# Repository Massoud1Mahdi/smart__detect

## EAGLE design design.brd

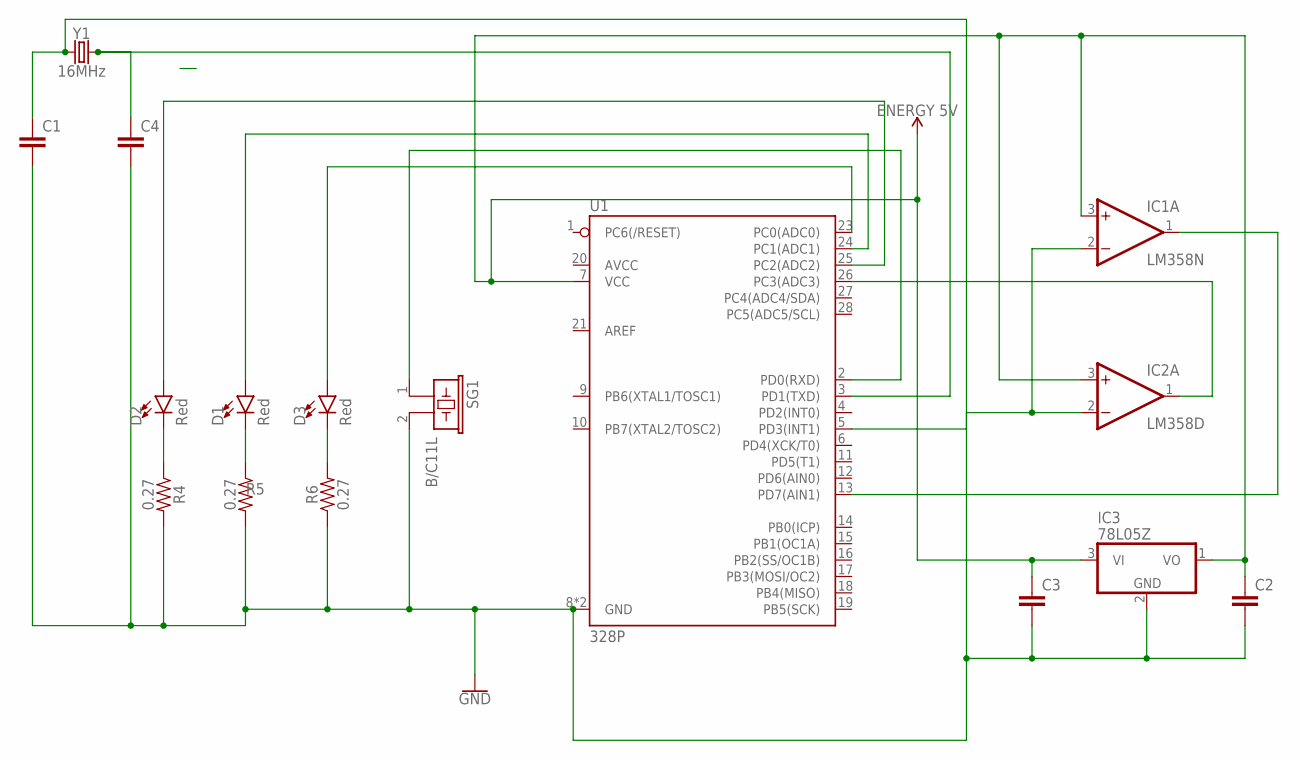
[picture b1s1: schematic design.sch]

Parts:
C1, C2, C3, C4: C2,5-3; C2.5-3
D1, D2, D3: Red; LED-0603
IC1: LM358N; DIL08
IC2: LM358D; SO08
IC3: 78L05Z; TO92
R4, R5, R6: 0.27; 0603
SG1: B/C11L
U1: 328P; DIP28
Y1: 16MHz; HC49US

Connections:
GND: C1.2, C2.2, C3.2, C4.2, IC1.2 (-IN), IC2.2 (-IN), IC3.2 (GND), R4.2, R5.2, R6.1, SG1.2, U1.8 (GND), U1.22 (GND)
unnamed: IC2.1 (OUT), U1.26 (PC3(ADC3))
unnamed: D2.C, R4.1
unnamed: D1.C, R5.1
unnamed: D3.C, R6.2
unnamed: D2.A, U1.25 (PC2(ADC2))
unnamed: D3.A, U1.23 (PC0(ADC0))
unnamed: D1.A, U1.24 (PC1(ADC1))
unnamed: SG1.1, U1.2 (PD0(RXD))
unnamed: C4.1, U1.3 (PD1(TXD)), Y1.2
unnamed: C1.1, U1.5 (PD3(INT1)), Y1.1
unnamed: IC1.1 (OUT), U1.13 (PD7(AIN1))
V+: IC1.8 (V+), IC2.8 (V+)
V-: IC1.4 (V-), IC2.4 (V-)
V_BATT: C2.1, C3.1, IC1.3 (+IN), IC2.3 (+IN), IC3.1 (VO), IC3.3 (VI), U1.7 (VCC)

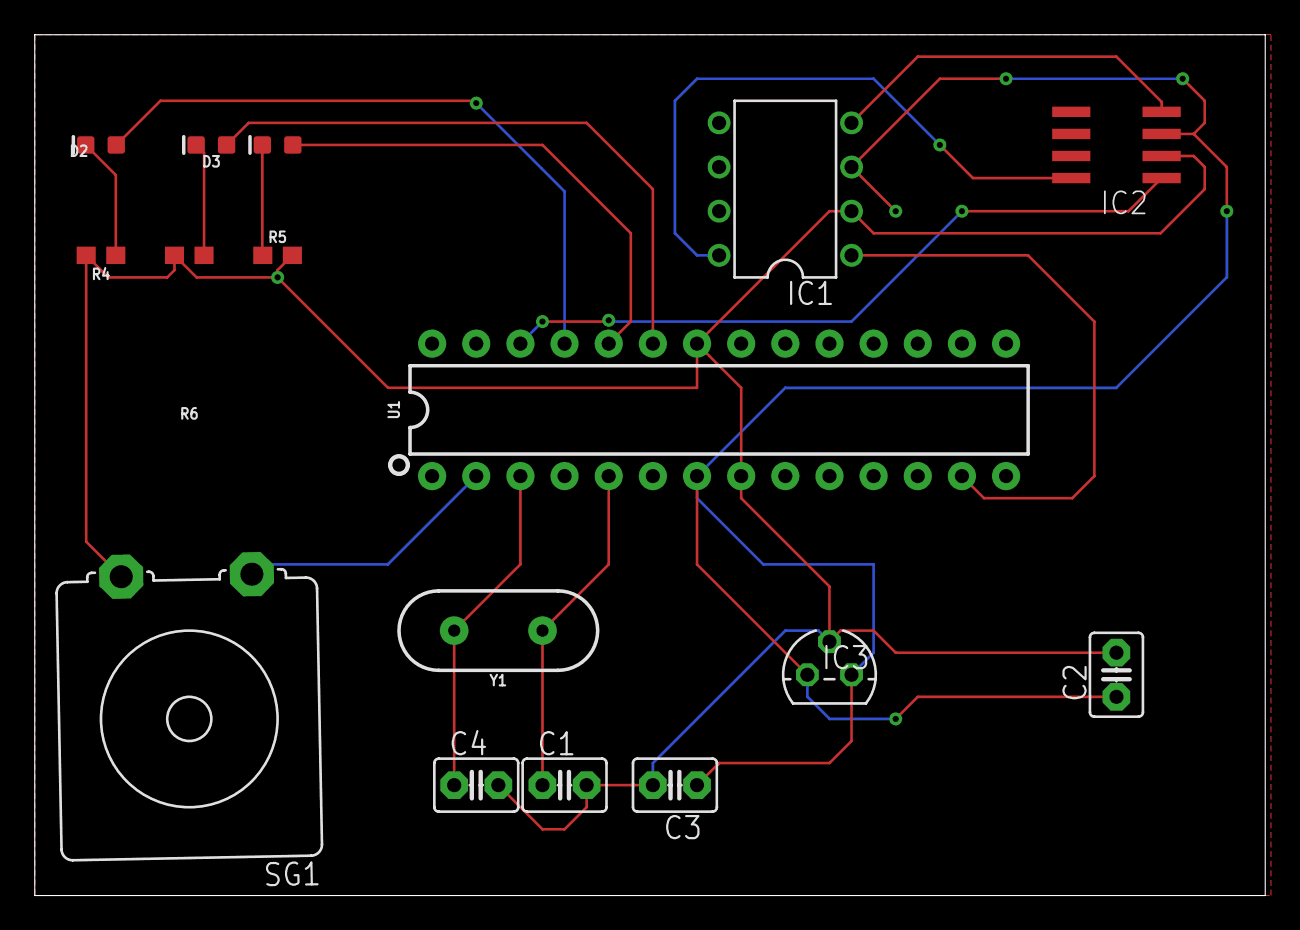
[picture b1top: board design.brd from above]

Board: 2 copper layers, 70.8 x 49.5 mm, 16 parts (0 on the bottom side), 15 nets.

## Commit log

2026-01-17 smart detect
    This workflow automates the deployment of static content to GitHub Pages upon pushes to the main branch or manual triggers.

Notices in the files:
parts and their libraries:
SparkFun-IC-Microcontroller: Licensing: Creative Commons ShareAlike 4.0 International - https://creativecommons.org/licenses/by-sa/4.0
